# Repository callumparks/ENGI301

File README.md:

# ENGI301

Repositroy for ENGI 301 Course Work

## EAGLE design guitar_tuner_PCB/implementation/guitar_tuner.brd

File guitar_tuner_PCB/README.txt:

~𝖗𝖊𝖆𝖉𝖒𝖊============== ~~ R E A D  M E ~~ ==============𝖗𝖊𝖆𝖉𝖒𝖊~
	(c) Callum Parks
	12/16/2020

Contained in Directory:
	
	Docs
		.gerbv verification
		.pdf schematics
		bill of meterials .txt
	Gerber
		.gbr files for manufacture
	Implementation
		Board .brd
		Schematics .sch
		Library .lbr

This is a PCB for a guitar tuner which plays a chosen not 
and controls a servo. This project is based off of a 
pocketbeagle computer. INcluded in this directory are all 
resources used in the development of this project.

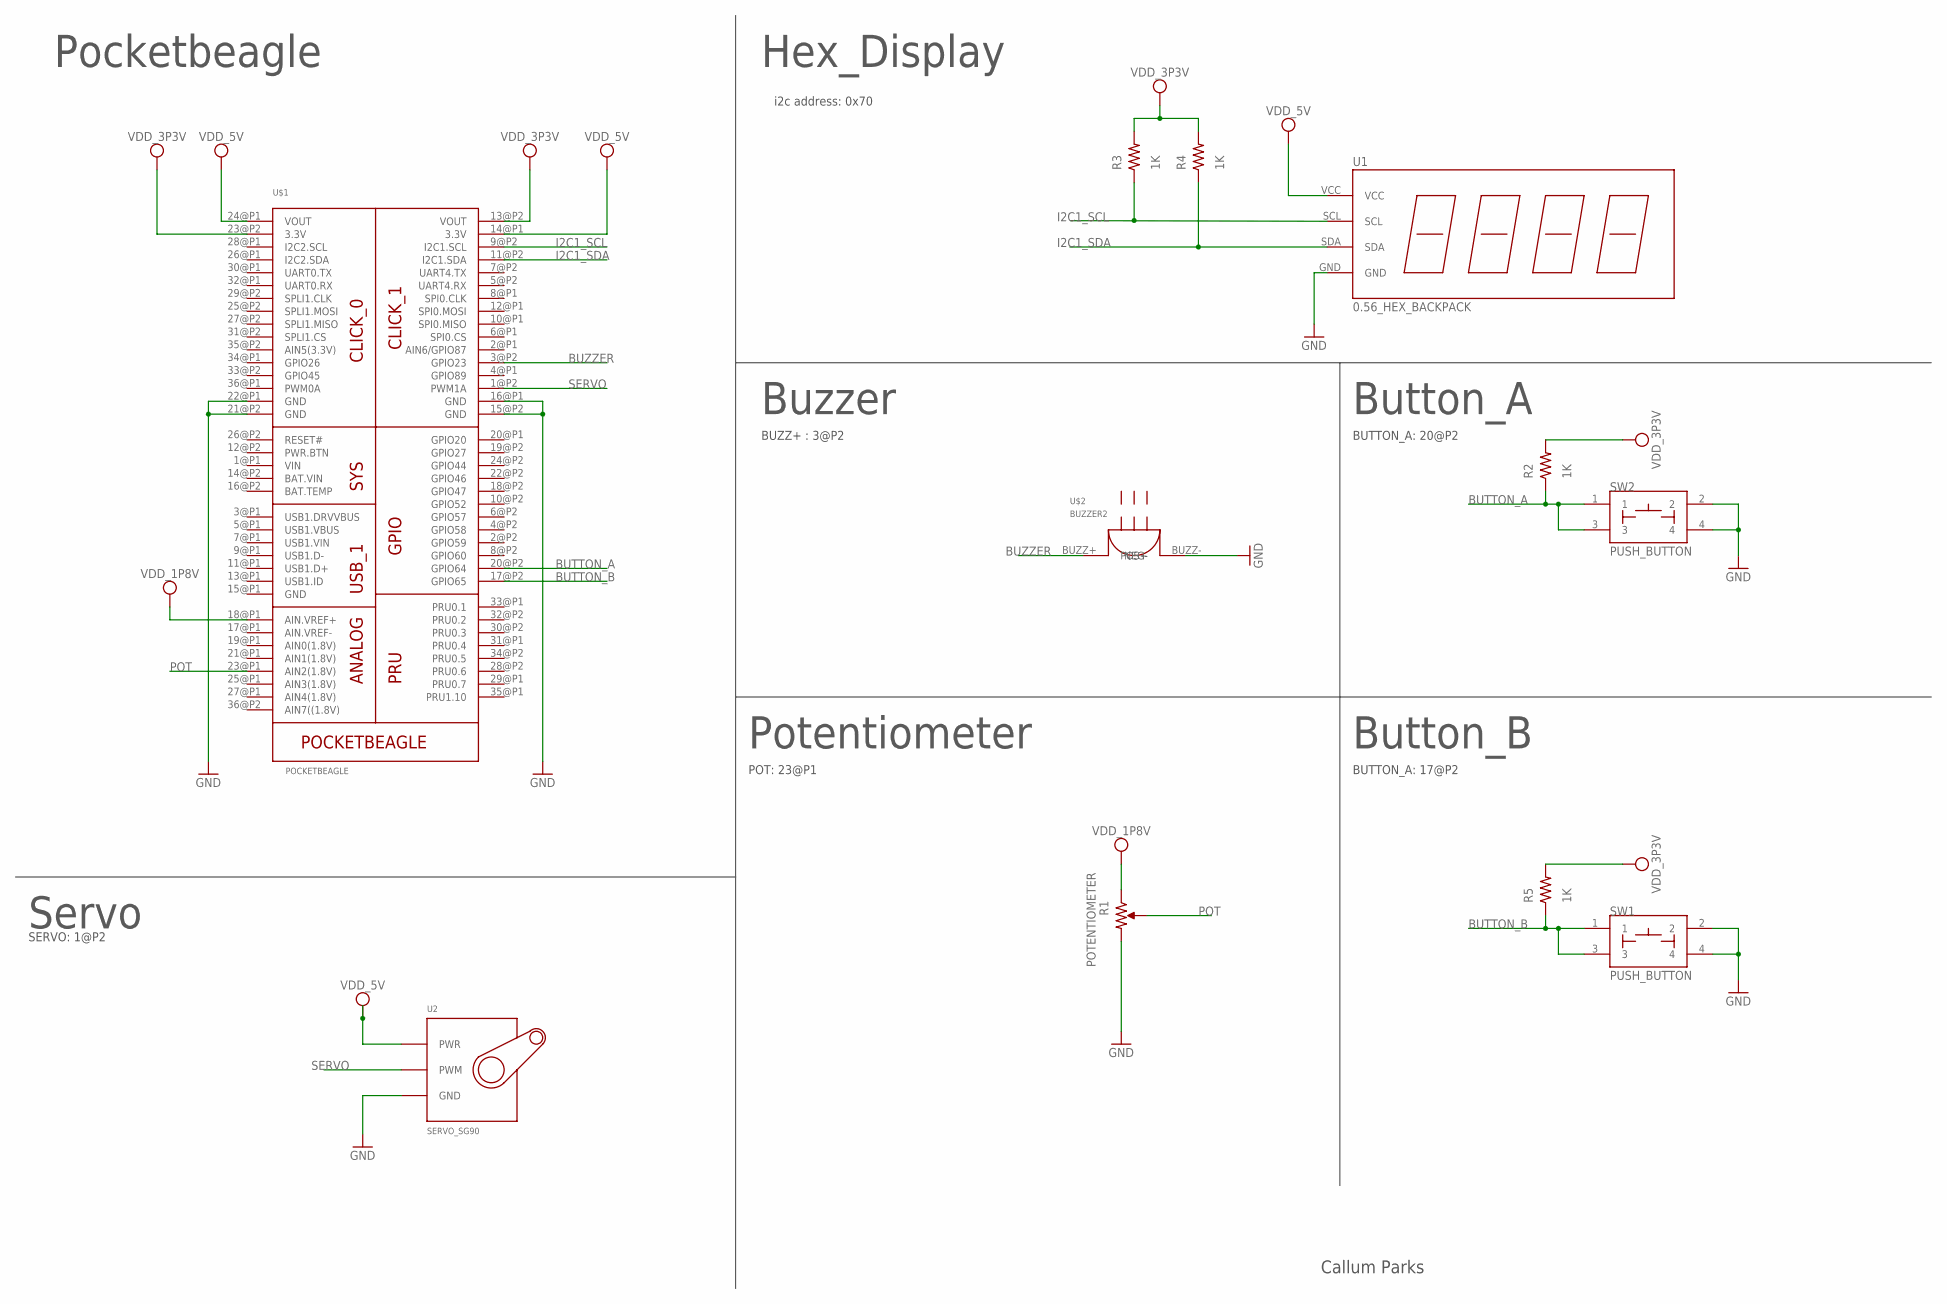
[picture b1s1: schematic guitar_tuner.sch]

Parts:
R1: POTENTIOMETER; POT-PO90S
R2, R3, R4, R5: 1K; R0402
SW1, SW2: PUSH_BUTTON; BUTTON_12.5MM
U1: 0.56_HEX_BACKPACK
U2: SERVO_SG90; SERVO-X1
U$1: POCKETBEAGLE
U$2: BUZZER2

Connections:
BUTTON_A: R2.1, SW2.1, SW2.3, U$1.20@P2 (GPIO64)
BUTTON_B: R5.1, SW1.1, SW1.3, U$1.17@P2 (GPIO65)
BUZZER: U$1.3@P2 (GPIO23), U$2.BUZZ+ (POS+)
GND: R1.CW, SW1.2, SW1.4, SW2.2, SW2.4, U1.GND, U2.GND, U$1.15@P2 (GND), U$1.16@P1 (GND), U$1.21@P2 (GND), U$1.22@P1 (GND), U$2.BUZZ- (NEG-)
I2C1_SCL: U1.SCL, U$1.9@P2 (I2C1.SCL)
I2C1_SDA: R4.1, U1.SDA, U$1.11@P2 (I2C1.SDA)
POT: R1.S, U$1.23@P1 (AIN2(1.8V))
SERVO: U2.SIG (PWM), U$1.1@P2 (PWM1A)
VDD_3P3V: R1.CCW, R2.2, R3.2, R4.2, R5.2, U$1.13@P2 (VOUT), U$1.18@P1 (AIN.VREF+), U$1.23@P2 (3.3V)
VDD_5V: U1.VCC, U2.PWR, U$1.14@P1 (3.3V), U$1.24@P1 (VOUT)

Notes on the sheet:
Pocketbeagle
Hex_Display
Buzzer
Button_A
Potentiometer
Button_B
Servo
i2c address: 0x70
BUZZ+ : 3@P2
SERVO: 1@P2
BUTTON_A: 17@P2
BUTTON_A: 20@P2
POT: 23@P1
Callum Parks

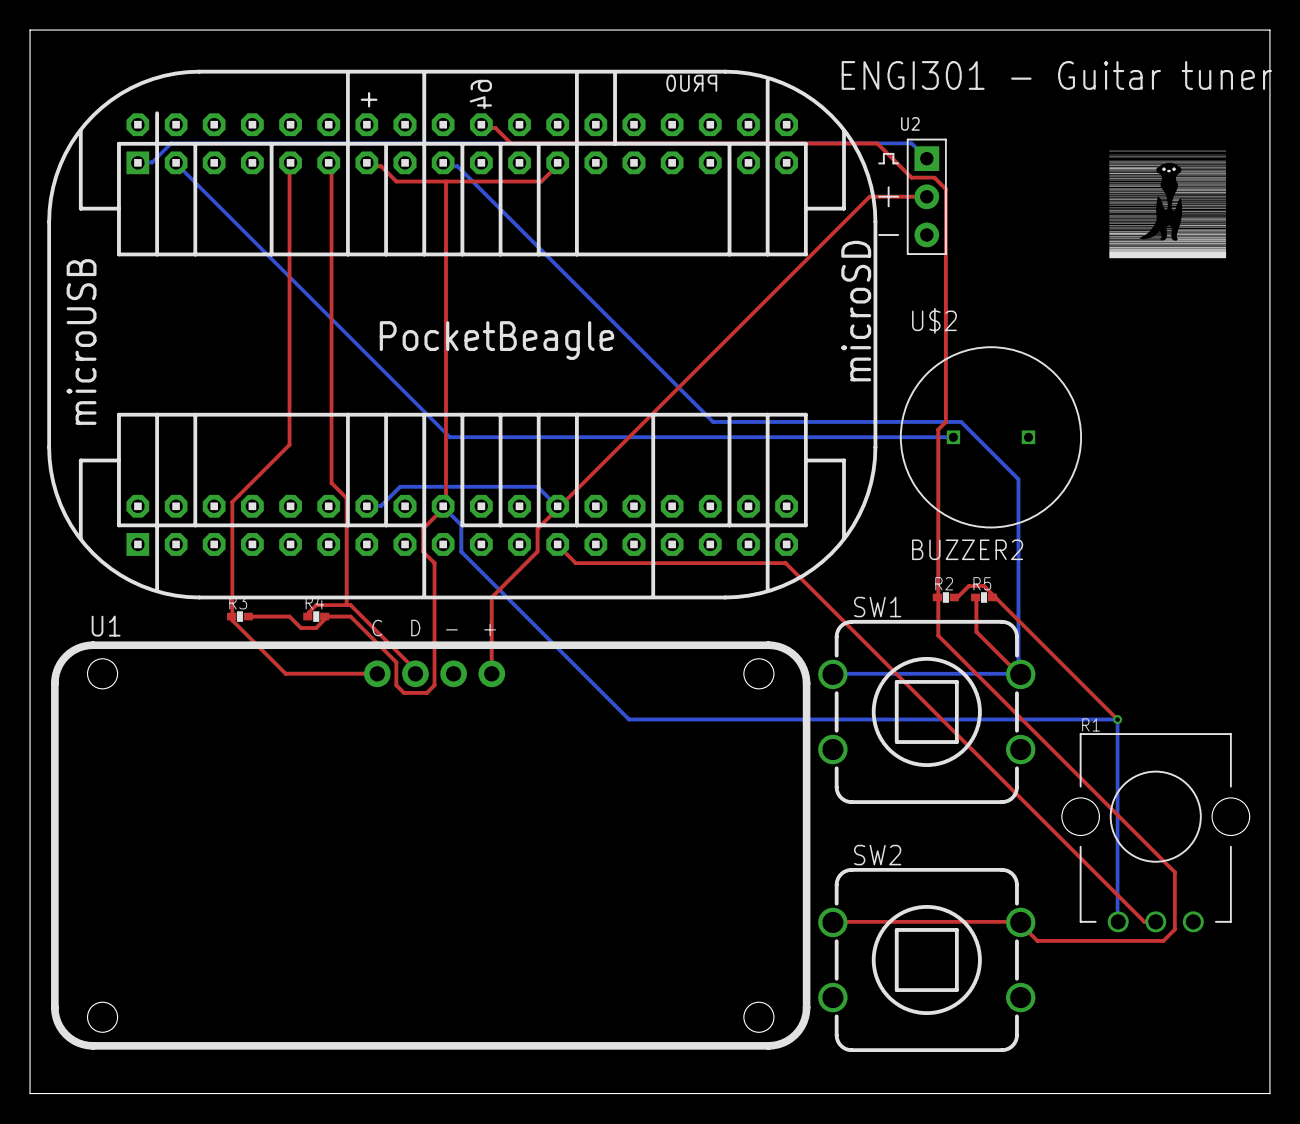
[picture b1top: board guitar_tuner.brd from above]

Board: 4 copper layers, 82.5 x 70.8 mm, 11 parts (0 on the bottom side), 10 nets.

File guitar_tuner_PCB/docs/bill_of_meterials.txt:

Partlist exported from C:/Users/kinga/OneDrive/Documents/junioryr/Engi301/EAGLE guitar tuner/guitar_tuner.sch at 12/16/2020 5:29 PM

Qty Value             Device            Package           Parts          Description                                 
1   0.56_HEX_BACKPACK 0.56_HEX_BACKPACK 0.56_HEX_BACKPACK U1             0.56" LED HEX Backback - Adafruit HT16K33 - 
4   1K                R_R0402           R0402             R2, R3, R4, R5 RESISTOR, American symbol                   
1   BUZZER2           BUZZER2           BUZZER2           U$2                                                        
1   POCKETBEAGLE      POCKETBEAGLE      POCKETBEAGLE      U$1                                                        
1   POTENTIOMETER     POTENTIOMETER     POT-PO90S         R1             Potentiometer - Examples:                   
2   PUSH_BUTTON       PUSH_BUTTON       BUTTON_12.5MM     SW1, SW2                                                   
1   SERVO_SG90        SERVO_SG90        SERVO-X1          U2

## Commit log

2020-09-15 Update README.md
    Updating readme.md
2020-10-14 Files
2020-11-14 Final
2020-11-23 found pptx
2020-12-17 step1
